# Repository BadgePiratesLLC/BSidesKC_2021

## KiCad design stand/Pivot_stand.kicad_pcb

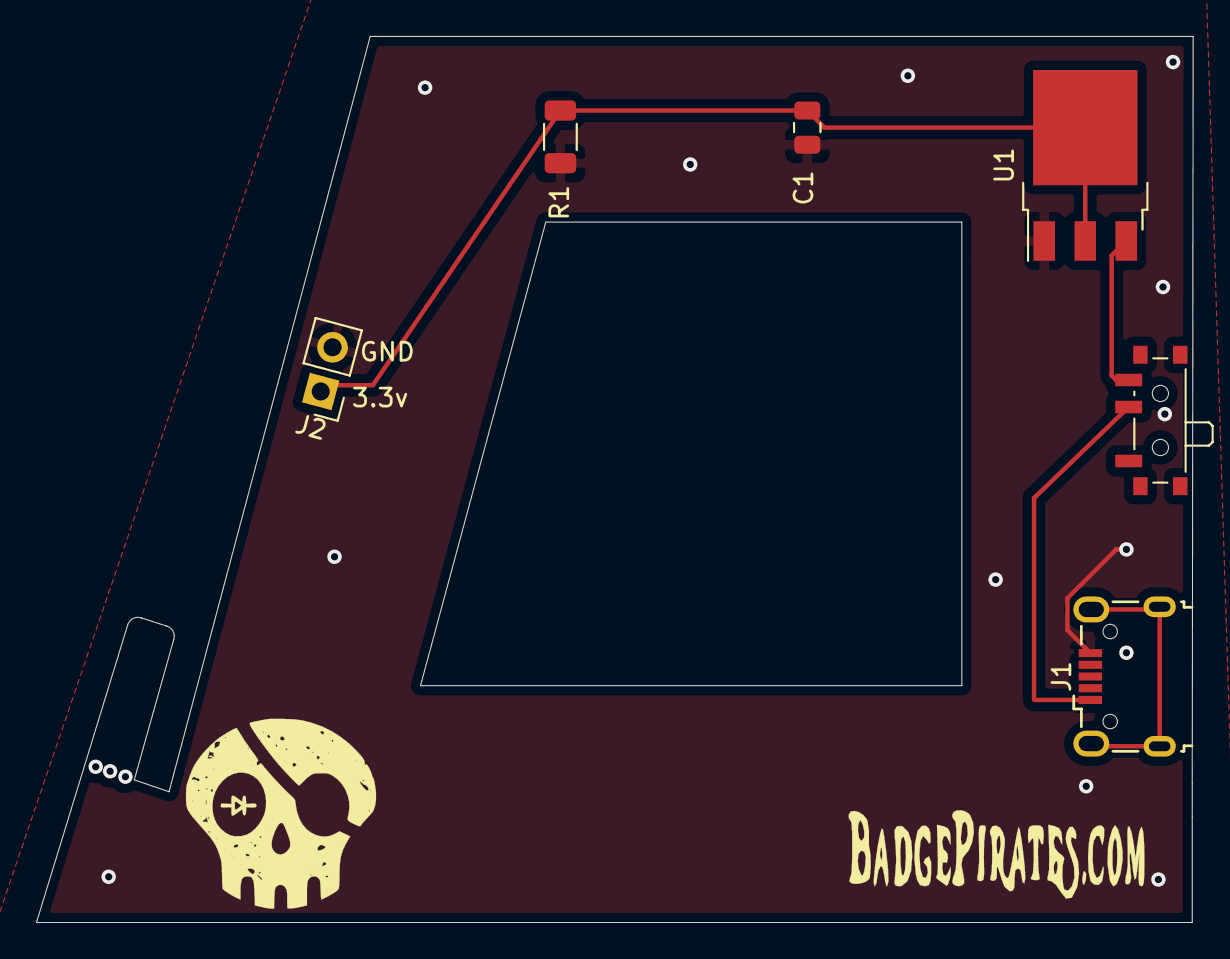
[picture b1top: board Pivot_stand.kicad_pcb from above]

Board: 2 copper layers, 64.3 x 49.2 mm, 6 parts (0 on the bottom side), 4 nets.

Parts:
C1: CP1; C_0805_2012Metric
I/O: SW_DPDT_x2; SW_SPDT_PCM12
J1: USB_B_Micro; USB_Micro-B_Wuerth_629105150521
J2: Conn_01x02_Male; PinHeader_1x02_P2.54mm_Vertical
R1: R; R_1206_3216Metric
U1: IFX27001TFV33; TO-252-3_TabPin2

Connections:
+3V3: C1.1, J2.1, R1.1, U1.2
GND: C1.2, J1.5, J2.2, R1.2, U1.1
unnamed: I/O.2, J1.1
unnamed: I/O.3, U1.3

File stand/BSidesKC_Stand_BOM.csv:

Id,Designator,Package,Quantity,Designation,Supplier and ref
1,I/O,SW_SPDT_PCM12,1,SW_DPDT_x2,https://www.digikey.com/en/products/detail/c-k/PCM12SMTR/1640112
2,J2,PinHeader_1x02_P2.54mm_Vertical,1,Conn_01x02_Male,https://www.digikey.com/en/products/detail/w%C3%BCrth-elektr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
9,U1,TO-252-3_TabPin2,1,IFX27001TFV33,https://www.mouser.com/ProductDetail/Infineon-Technologies/I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
10,R1,R_1206_3216Metric,1,R,<Need Measurement>
11,J1,USB_Micro-B_Wuerth_629105150521,1,USB_B_Micro,https://www.mouser.com/ProductDetail/Wurth-Elektronik/629105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
12,C1,C_0805_2012Metric,1,CP1,<Need Measurement>
